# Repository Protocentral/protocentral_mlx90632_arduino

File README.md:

## Protocentral MLX90632

**ProtoCentral Infrared Non-Contact Thermometer (Qwiic) – MLX90632** is a miniature breakout for accurate non-contact temperature measurement, especially in thermally challenging environments.

It supports any microcontroller for interface with the integrated logic level converter on-board regulator and now compatible with an integrated QWIIC-connectors for complete compatibility with the QWIIC Ecosystem The temperature measured by MLX90632 is the average temperature of all the objects in its field of view. The wavelength pass band of the optical filter integrated into the sensor ranges from 2 to 14Î¼m.This board is directly compatible with the QWIIC connector standard from Sparkfun. This means easy plug-and-play usage with all QWIIC-compatible shields and boards.

### Connection with Arduino

|Protocentral MLX90632 pin label| Arduino Connection   |Pin Function      |
|----------------- |:--------------------:|-----------------:|
| SDA              | A4                  |  Serial Data      |
| SCL              | A5                  |  Serial Clock     |
| Vin              | 5V                  |  Power            |
| GND              | Gnd                 |  Gnd              |

License Information
===================

This product is open source! Both, our hardware and software are open source and licensed under the following licenses:

Hardware
---------

**All hardware is released under [Creative Commons Share-alike 4.0 International](http://creativecommons.org/licenses/by-sa/4.0/).**

You are free to:

* Share — copy and redistribute the material in any medium or format
* Adapt — remix, transform, and build upon the material for any purpose, even commercially.
The licensor cannot revoke these freedoms as long as you follow the license terms.

Under the following terms:

* Attribution — You must give appropriate credit, provide a link to the license, and indicate if changes were made. You may do so in any reasonable manner, but not in any way that suggests the licensor endorses you or your use.
* ShareAlike — If you remix, transform, or build upon the material, you must distribute your contributions under the same license as the original.

Software
--------

**All software is released under the MIT License(http://opensource.org/licenses/MIT).**

THE SOFTWARE IS PROVIDED "AS IS", WITHOUT WARRANTY OF ANY KIND, EXPRESS OR IMPLIED, INCLUDING BUT NOT LIMITED TO THE WARRANTIES OF MERCHANTABILITY, FITNESS FOR A PARTICULAR PURPOSE AND NONINFRINGEMENT. IN NO EVENT SHALL THE AUTHORS OR COPYRIGHT HOLDERS BE LIABLE FOR ANY CLAIM, DAMAGES OR OTHER LIABILITY, WHETHER IN AN ACTION OF CONTRACT, TORT OR OTHERWISE, ARISING FROM, OUT OF OR IN CONNECTION WITH THE SOFTWARE OR THE USE OR OTHER DEALINGS IN THE SOFTWARE.

Please check [*LICENSE.md*](LICENSE.md) for detailed license descriptions.

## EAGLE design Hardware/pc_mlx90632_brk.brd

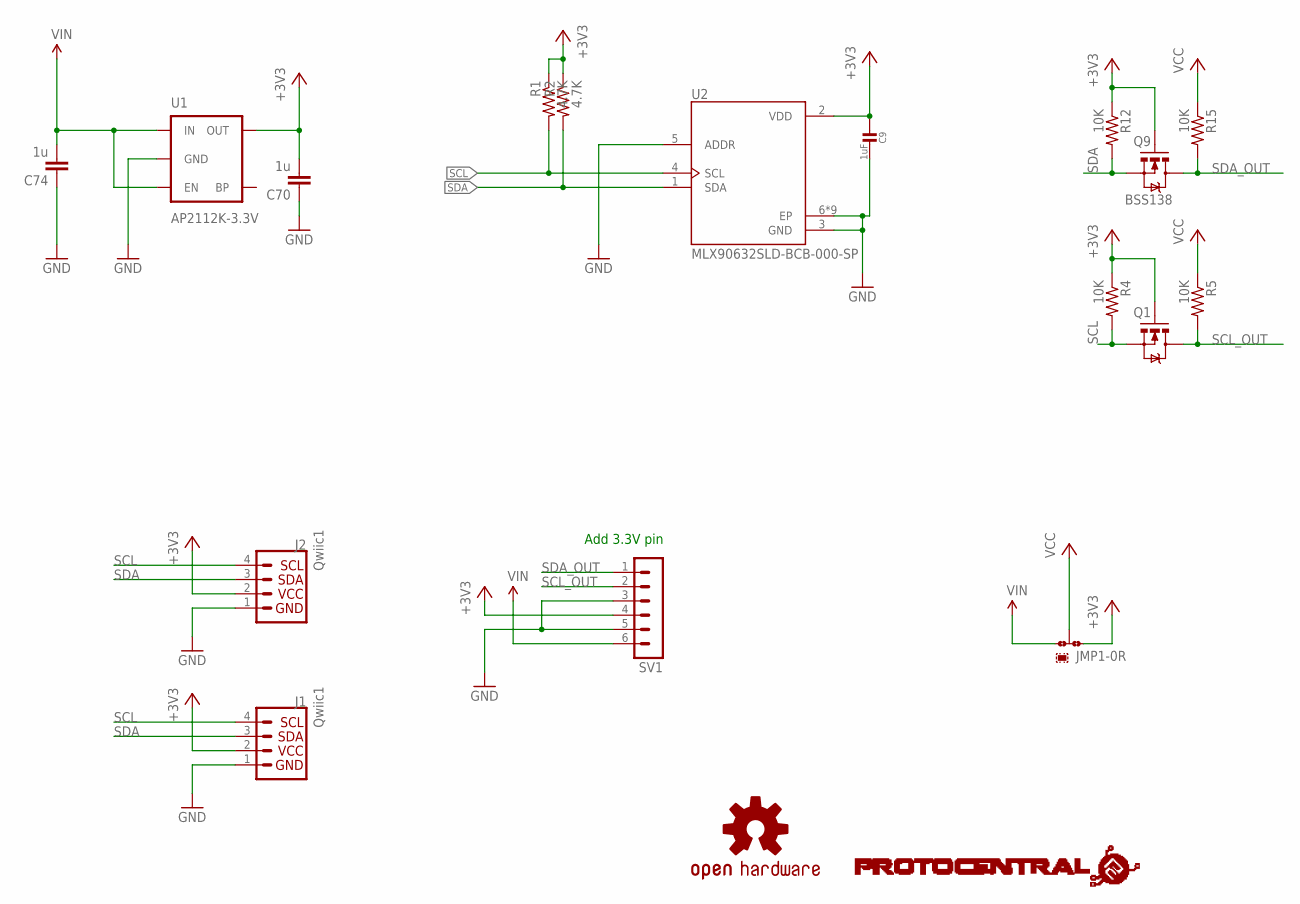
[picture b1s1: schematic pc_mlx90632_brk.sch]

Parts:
C9: 1uF; _0402
C70, C74: 1u; C0805
J1, J2: Qwiic1; 1X04_1MM_RA
JMP1: 0R-JUMPA; A0R-JMP-0402
Q1, Q9: BSS138; SOT23-3
R1, R2: 4.7K; R0402
R4, R5, R12, R15: 10K; 0805
SV1: MA06-1
U1: AP2112K-3.3V; SOT23-5
U2: MLX90632SLD-BCB-000-SP; XDCR_MLX90632SLD-BCB-000-SP
U$5: PROTY-LOGO; LOGO-PROTY
U$7: OSHW-LOGOS; OSHW-LOGO-S

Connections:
+3V3: C9.1, C70.2, J1.2, J2.2, JMP1.3, Q1.1 (G), Q9.1 (G), R1.1, R2.1, R4.1, R12.1, SV1.4, U1.5 (OUT), U2.2 (VDD)
GND: C9.2, C70.1, C74.1, J1.1, J2.1, SV1.3, SV1.5, U1.2 (GND), U2.3 (GND), U2.5 (ADDR), U2.6 (EP), U2.6.1 (EP), U2.6.2 (EP), U2.6.3 (EP), U2.6.4 (EP), U2.6.5 (EP), U2.6.6 (EP), U2.6.7 (EP), U2.6.8 (EP)
SCL: J1.4, J2.4, Q1.2 (S), R1.2, R4.2, U2.4 (SCL)
SCL_OUT: Q1.3 (D), R5.2, SV1.2
SDA: J1.3, J2.3, Q9.2 (S), R2.2, R12.2, U2.1 (SDA)
SDA_OUT: Q9.3 (D), R15.2, SV1.1
VCC: JMP1.2, R5.1, R15.1
VIN: C74.2, JMP1.1, SV1.6, U1.1 (IN), U1.3 (EN)

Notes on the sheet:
Add 3.3V pin

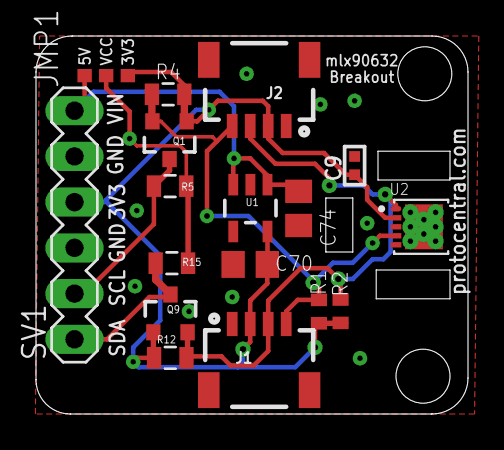
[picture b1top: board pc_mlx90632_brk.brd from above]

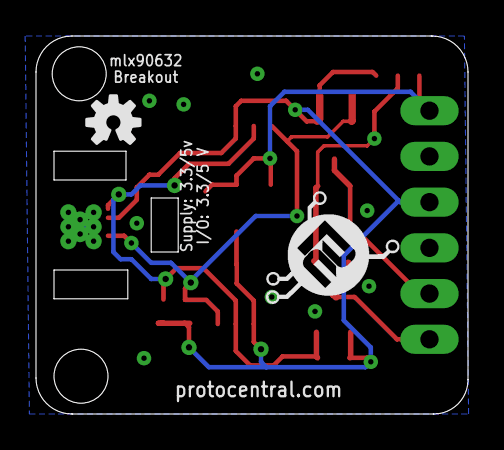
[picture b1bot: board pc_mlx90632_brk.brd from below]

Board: 4 copper layers, 24.0 x 21.0 mm, 19 parts (2 on the bottom side), 8 nets.

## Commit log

2020-10-27 Added hardware files
2020-10-27 added software
2020-10-28 Edited README, added LICENSE

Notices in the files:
README.md:
CC-BY-SA-4.0
parts and their libraries:
SparkFun-PowerIC: Licensing: Creative Commons ShareAlike 4.0 International - https://creativecommons.org/licenses/by-sa/4.0
microbuilder: This work is placed in the public domain, and may be freely used for commercial and non-commercial work with the following conditions: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
